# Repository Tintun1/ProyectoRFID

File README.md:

# Proyecto RFID/NFC con App Web

Es una solución eficaz para cuando se necesita restringir el acceso a un área determinada y queremos tener la lista de usuarios permitidos en una base de datos segura con una aplicación web para la interfaz grafica del control de acceso.

## Participantes

- Fernandez Joaquín - Programación
- Lescano Cristian - Fabricación de PCB
- Lacuadra Catalina - Montaje y diseño
- Macre Geremias -  Montaje y diseño

## Aplicación

Para implementarlo como control de acceso a un área, necesitamos ajustar unos parámetros del microcontrolador, para que se pueda conectar a la red wifi

[https://github.com/Tintun1/ProyectoRFID/blob/main/Codigo ESP32/nfcReader/nfcReader.ino](https://github.com/Tintun1/ProyectoRFID/blob/main/Codigo%20ESP32/nfcReader/nfcReader.ino)

una vez configurado, el microcontrolador ya tendrá acceso a la red wifi.

Para poder vincular nuestra base de datos lo debemos hacer desde este archivo:

[https://github.com/Tintun1/ProyectoRFID/blob/main/AppWeb/con_db.php](https://github.com/Tintun1/ProyectoRFID/blob/main/AppWeb/con_db.php)

se debería de poner las credenciales correspondientes a la base de datos y en [https://github.com/Tintun1/ProyectoRFID/blob/main/AppWeb/ESP32/esp32_update.php](https://github.com/Tintun1/ProyectoRFID/blob/main/AppWeb/ESP32/esp32_update.php)

tendremos la API de la conexión de la base de datos con el microcontrolador que se puede modificar a gusto.

Para poder hacer funcionar  la aplicación web necesitaremos hostear nuestro servidor, una de las formas es usar XAMMP que nos facilita el host de la pagina de manera local

## Usos

Luego de configurar y ajustar los parámetros a nuestra comodidad, dispondremos de un control de acceso funcional. Lo único que hay que hacer para probar que funcione correctamente es verificar si el host de la pagina anda correctamente, registrando nuestros datos en la pagina para acceder a nuestro panel admin y poder registrar tarjetas nuevas a la base de datos, una vez registrada probar si el control de acceso lee nuestra tarjeta y que de la autorización.

## Esquemático

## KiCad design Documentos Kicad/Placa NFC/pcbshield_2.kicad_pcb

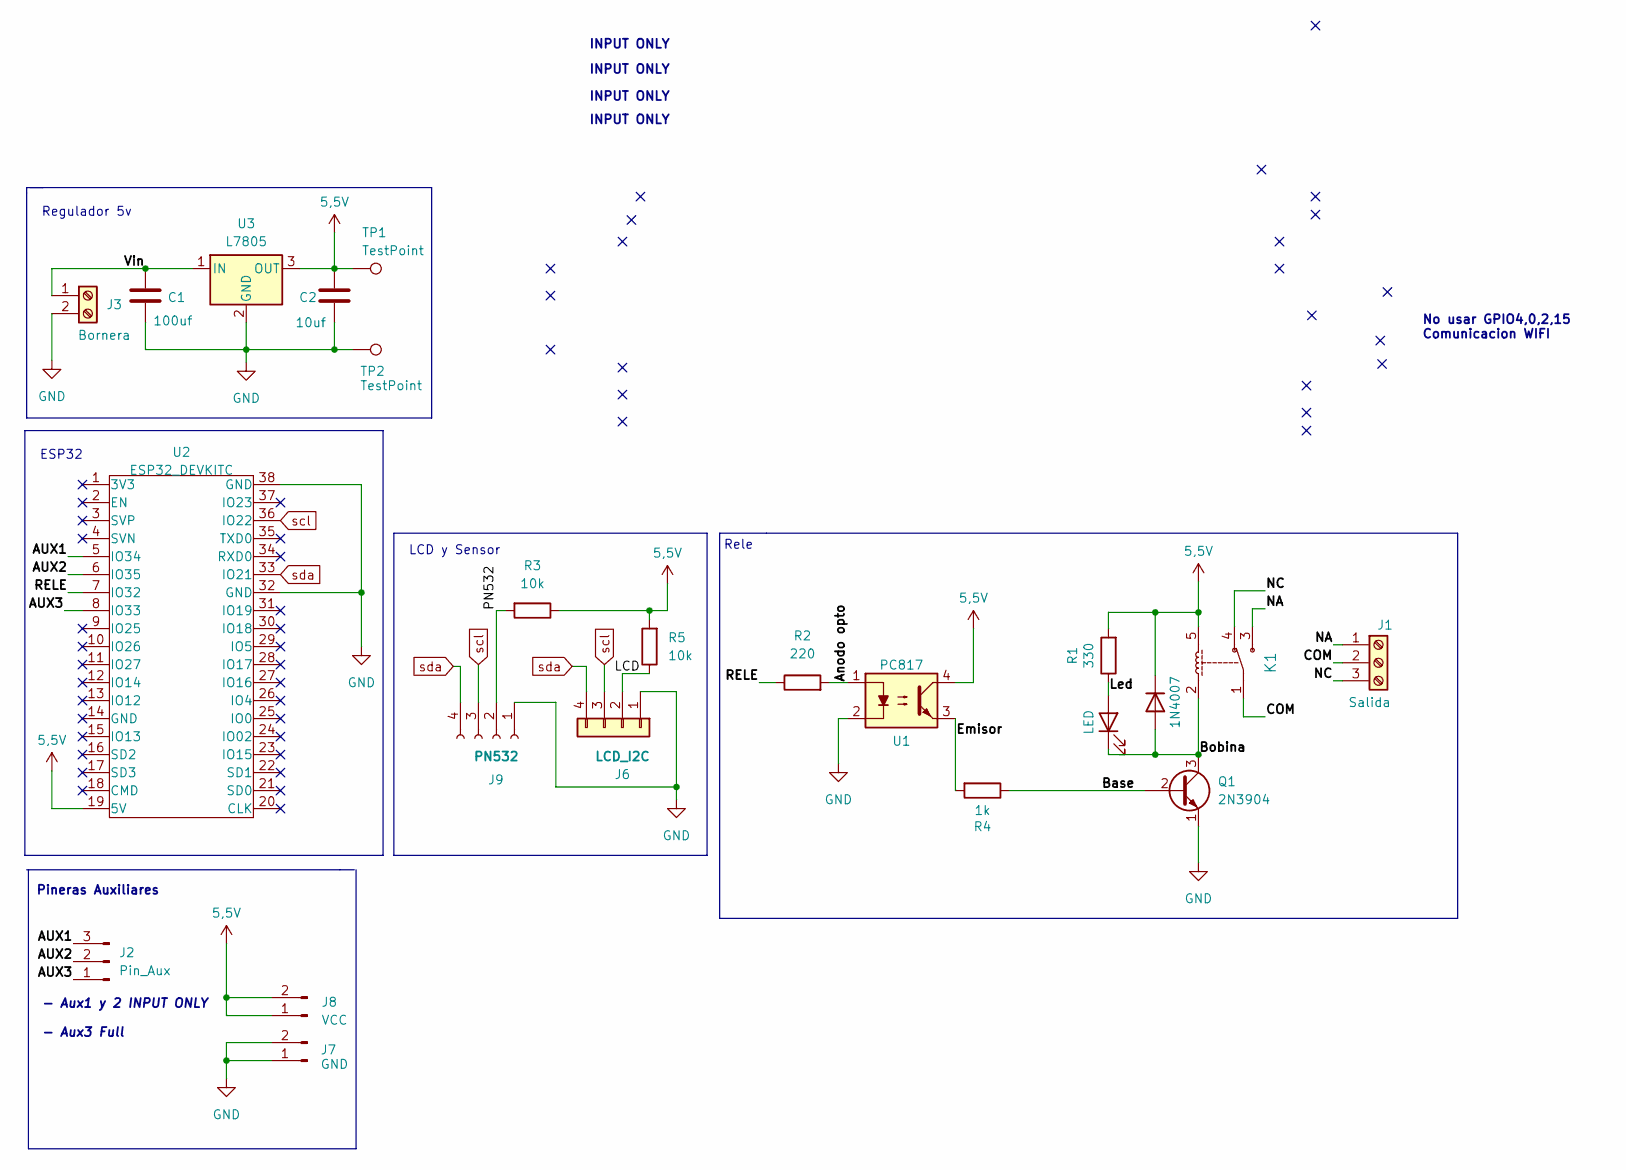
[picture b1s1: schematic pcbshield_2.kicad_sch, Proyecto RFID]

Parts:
C1: 100uf; CAP_ELEC_8x11.5mm
C2: 10uf; CAP_ELEC_8x11.5mm
D1: LED; led_3mm_red
D2: 1N4007; D_DO-41_SOD81_P10.16mm_Horizontal
J1: Salida; BORNERA3_AZUL
J2: Pin_Aux; Pin_Strip_3
J3: Bornera; BORNERA2_AZUL
J6: LCD_I2C; pin_strip_4
J7: GND; Pin_strip_2
J8: VCC; Pin_strip_2
J9: PN532; pin_strip_4
K1: RELAY_C; Relay_C
Q1: 2N3904; to92
R1: 330; RES0.3
R2: 220; RES0.3
R3, R5: 10k; RES0.3
R4: 1k; RES0.3
TP1, TP2: TestPoint; TestPoint_Loop_D2.50mm_Drill1.0mm_LowProfile
U1: PC817; DIP-4_W7.62mm
U2: ESP32_DEVKITC; ESP32 48x25 LEGIT
U3: L7805; TO-220

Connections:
5,5V: C2.1, D2.1 (K), J8.1, J8.2, K1.5, R1.2, R3.1, R5.2, TP1.1, U1.4, U2.19 (5V), U3.3 (OUT)
/AUX1: J2.3, U2.5 (IO34)
/AUX2: J2.2, U2.6 (IO35)
/AUX3: J2.1, U2.8 (IO33)
/Anodo opto: R2.2, U1.1
/Base: Q1.2 (B), R4.1
/Bobina: D1.1 (K), D2.2 (A), K1.2, Q1.3 (C)
/COM: J1.2, K1.1
/Emisor: R4.2, U1.3
/LCD: J6.2, R5.1
/Led: D1.2 (A), R1.1
/NA: J1.1, K1.3
/NC: J1.3, K1.4
/PN532: J9.2, R3.2
/RELE: R2.1, U2.7 (IO32)
/Vin: C1.1, J3.1, U3.1 (IN)
GND: C1.2, C2.2, J3.2, J6.1, J7.1, J7.2, J9.1, Q1.1 (E), TP2.1, U1.2, U2.32 (GND), U2.38 (GND), U3.2 (GND)
scl: J6.3, J9.3, U2.36 (IO22)
sda: J6.4, J9.4, U2.33 (IO21)

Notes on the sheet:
INPUT ONLY
Pineras Auxiliares
- Aux1 y 2 INPUT ONLY - Aux3 Full
Regulador 5v
ESP32
No usar GPIO4,0,2,15 Comunicacion WIFI
Rele
LCD y Sensor

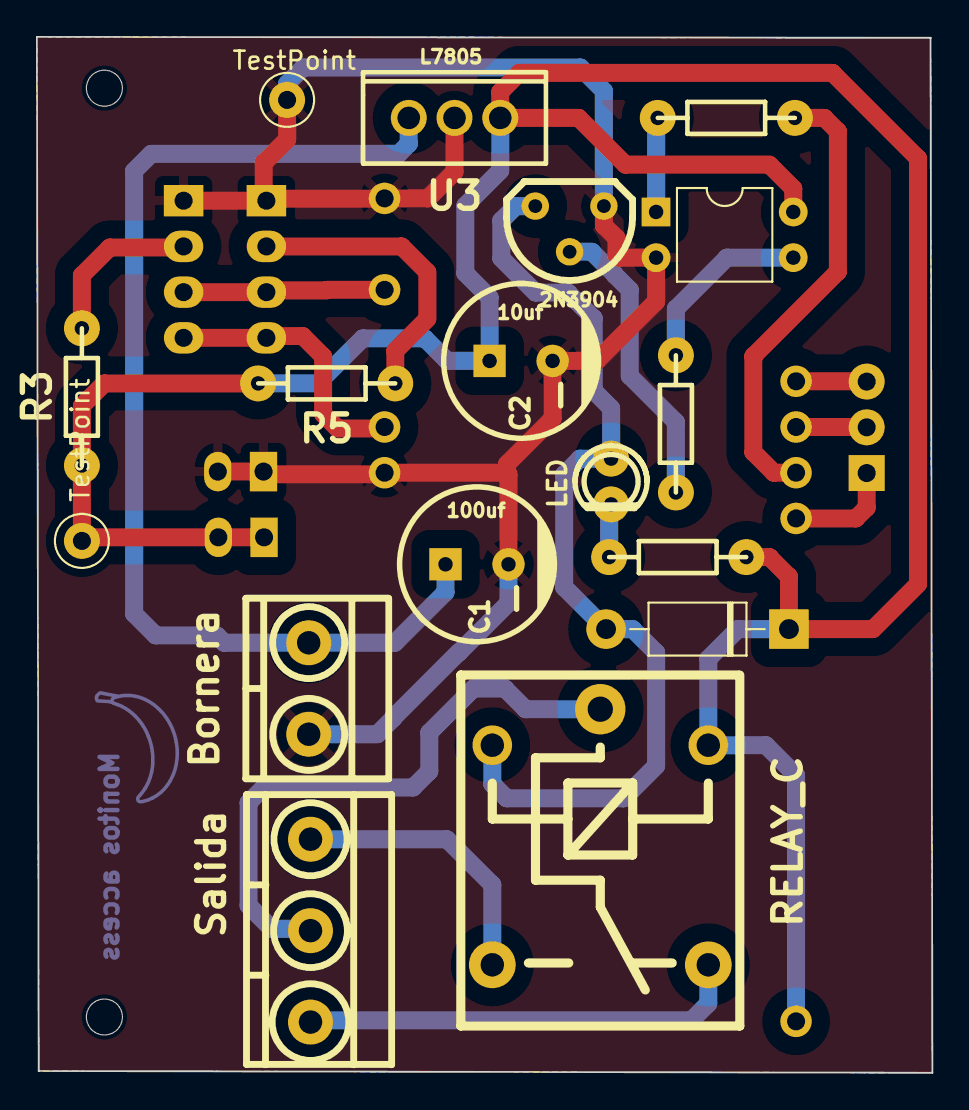
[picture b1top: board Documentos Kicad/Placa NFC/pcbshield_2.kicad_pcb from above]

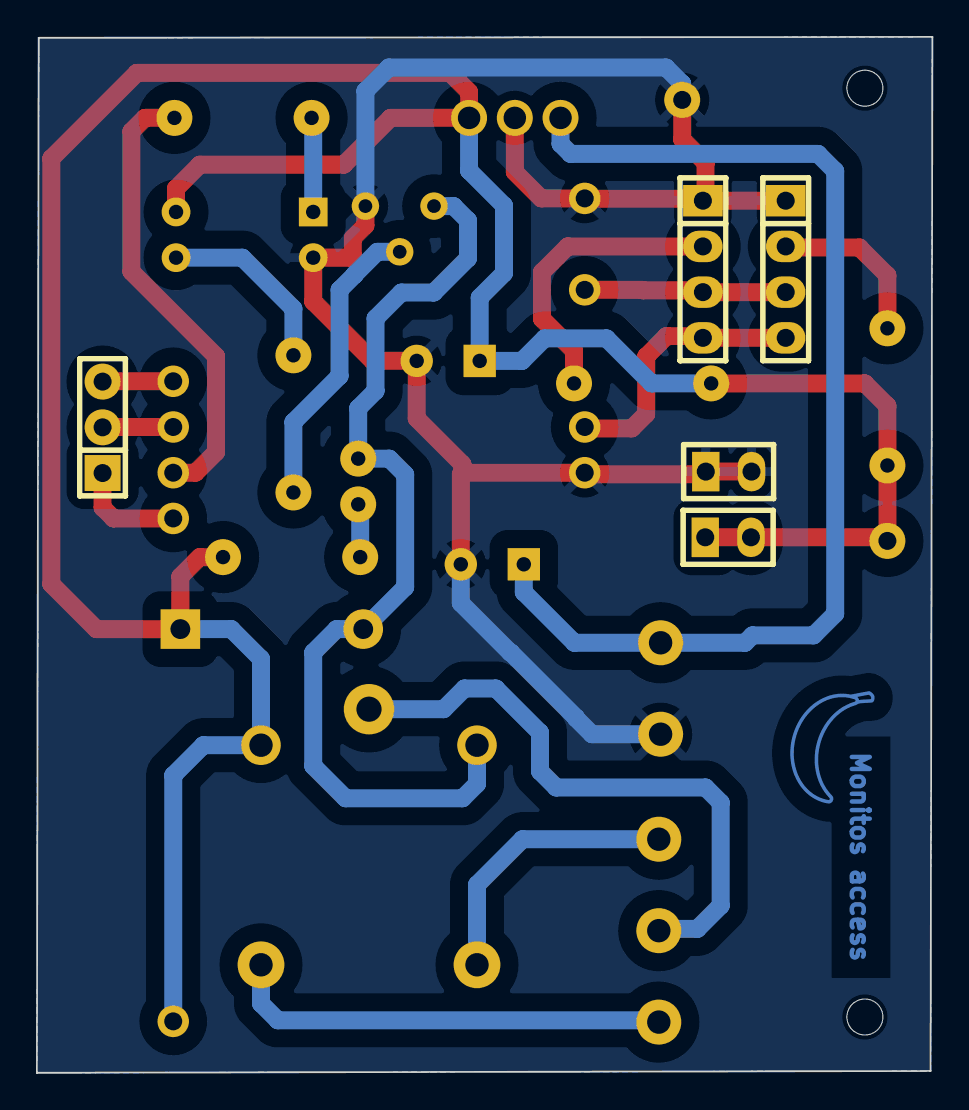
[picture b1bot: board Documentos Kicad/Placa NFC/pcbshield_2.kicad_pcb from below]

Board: 2 copper layers, 49.8 x 57.6 mm, 23 parts (6 on the bottom side), 19 nets.

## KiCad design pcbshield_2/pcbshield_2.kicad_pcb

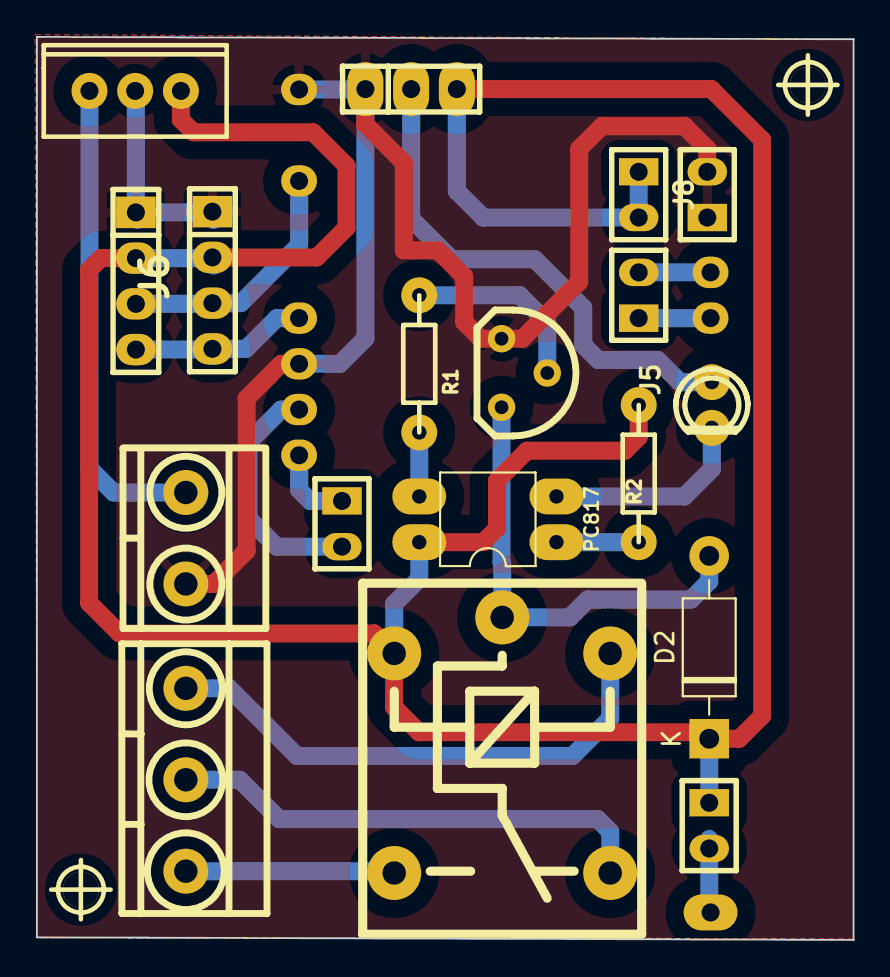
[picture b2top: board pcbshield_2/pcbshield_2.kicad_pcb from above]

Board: 2 copper layers, 45.4 x 50.2 mm, 21 parts (1 on the bottom side), 19 nets.

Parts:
D1: LED; led_3mm_red
D2: 1N4007; D_DO-41_SOD81_P10.16mm_Horizontal
J1: borneras; BORNERA3_AZUL
J2: pineras; Pin_Strip_3
J3: Screw_Terminal_01x02; BORNERA2_AZUL
J4, J5, J7, J8: Conn_01x02_Pin; Pin_strip_2
J6: Conn_01x04; pin_strip_4
JP1: Jumper
K1: RELAY_C; Relay_C
PC817: PC817; DIP-4_W7.62mm
Q1: 2N3904; to92
R1, R2: R; RES0.3
U2: ESP32_DEVKITC; ESP32 48x25 LEGIT
U3: L7805; TO-220
hole_2mm, hole_2mm#2: VAL**; hole_2mm
pn532: Conn_01x04_Socket; pin_strip_4

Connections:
/D18: J4.1, U2.30 (IO18)
/D19: J4.2, U2.31 (IO19)
/D34: J5.2, U2.5 (IO34)
/D35: J5.1, U2.6 (IO35)
GND: J2.1, J3.2, J6.1, J7.1, J7.2, Q1.1 (E), U2.32 (GND), U2.38 (GND), U3.2 (GND), pn532.1
unnamed: D1.2 (A), PC817.2
unnamed: D1.1 (K), J2.2
unnamed: D2.2 (A), K1.1, Q1.3 (C)
unnamed: J1.1, K1.5
unnamed: J1.2, K1.4
unnamed: J1.3, K1.3
unnamed: J3.1, U3.1 (IN)
unnamed: JP1.2 (B), U2.19 (5V)
unnamed: Q1.2 (B), R1.2
unnamed: PC817.3, R1.1
unnamed: PC817.1, R2.2
VCC: D2.1 (K), J2.3, J6.2, J8.1, J8.2, JP1.1 (A), K1.2, PC817.4, R2.1, U3.3 (OUT), pn532.2
scl: J6.3, U2.36 (IO22), pn532.3
sda: J6.4, U2.33 (IO21), pn532.4

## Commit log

2024-04-03 update
    release:
    publicaciones
    perfiles
    comunidad
2024-04-09 pcb
    pcb y esquematico
2024-04-10 pcb update
    3d model
2024-04-13 PCB 2
    pcb doble faz
2024-05-21 Actualizacion
    -Codigo de esp32 funcionando
    -Placa necesita correcciones,pero funciona
    -AppWeb funcionando
2024-05-21 README
